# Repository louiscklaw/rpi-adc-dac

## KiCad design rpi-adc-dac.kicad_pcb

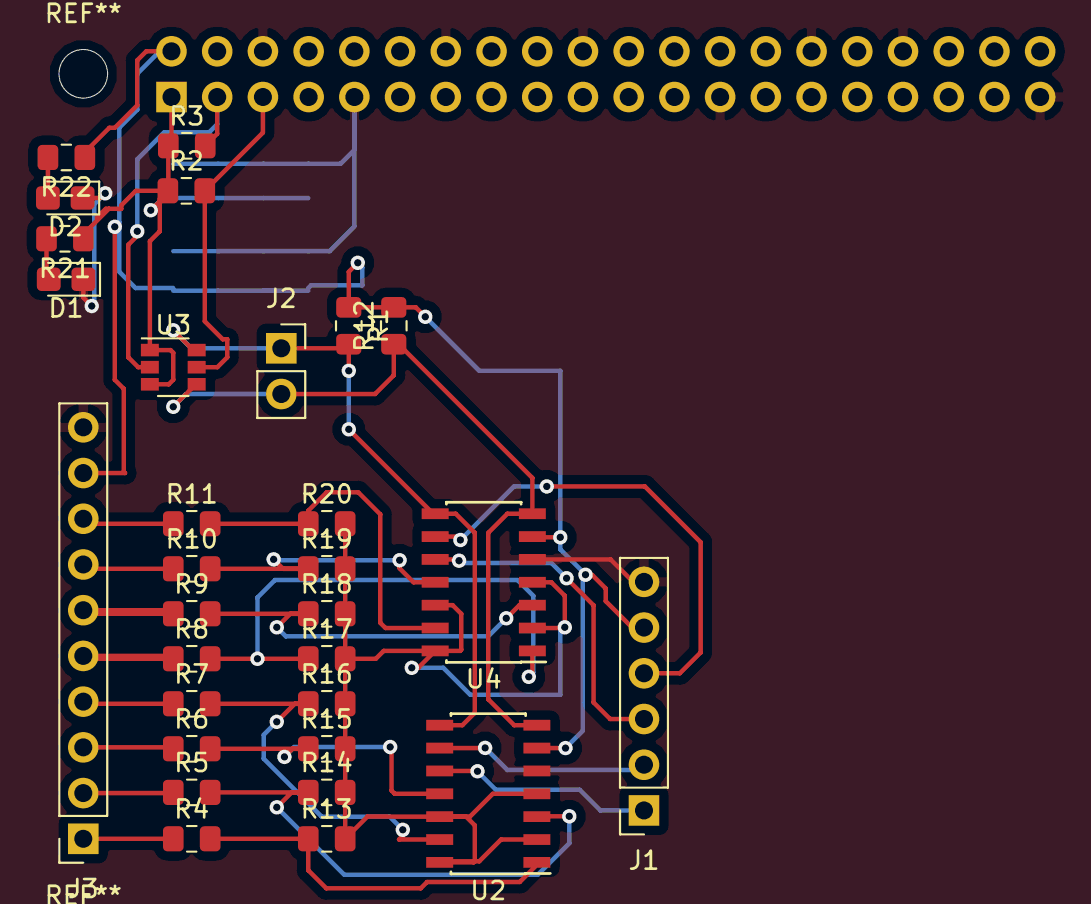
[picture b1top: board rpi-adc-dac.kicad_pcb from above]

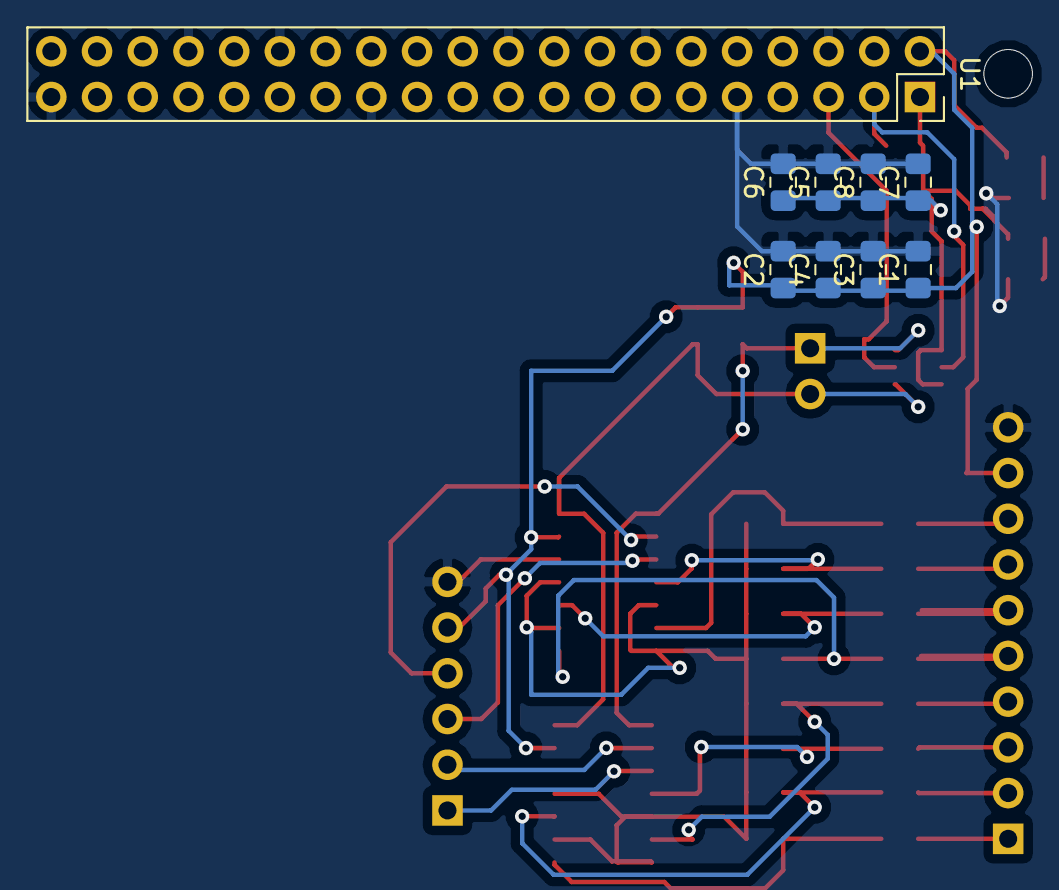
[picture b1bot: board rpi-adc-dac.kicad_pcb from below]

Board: 2 copper layers, 39 parts (9 on the bottom side), 30 nets.

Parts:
C1, C2, C3, C4, C5, C6, C7, C8: 105; C_0805_2012Metric_Pad1.15x1.40mm_HandSolder
D1: 3V3_STATUS; LED_0805_2012Metric_Castellated
D2: 5V_STATUS; LED_0805_2012Metric_Castellated
J1: Conn_01x02; PinSocket_1x06_P2.54mm_Vertical
J2: Conn_01x02; PinSocket_1x02_P2.54mm_Vertical
J3: Conn_01x02; PinSocket_1x10_P2.54mm_Vertical
R1, R2, R3, R4, R5, R6, R7, R8, R9, R11, R12: 103; R_0805_2012Metric_Pad1.15x1.40mm_HandSolder
R10, R14: R; R_0805_2012Metric_Pad1.15x1.40mm_HandSolder
R13, R15, R16, R17, R18, R19, R20: 682; R_0805_2012Metric_Pad1.15x1.40mm_HandSolder
R21: 511; R_0805_2012Metric_Pad1.15x1.40mm_HandSolder
R22: 102; R_0805_2012Metric_Pad1.15x1.40mm_HandSolder
U1: rpi-pin-out; PinSocket_2x20_P2.54mm_Vertical
U2, U4: MCP3424; SOIC-14_3.9x8.7mm_P1.27mm
U3: FDC6301N; SuperSOT-6

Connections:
+3V3: C5.1, C6.1, C7.1, C8.1, R2.1, R3.1, R21.1, U1.1, U3.1, U3.3
+5V: C1.1, C2.1, C3.1, C4.1, J1.5, J3.9, R1.1, R12.2, R22.1, U1.2, U2.6, U4.6
/GPIO0: R3.2, U1.3, U3.2
/GPIO1: R2.2, U1.5, U3.5
/SCL: J2.1, R1.2, U2.8, U3.6, U4.8
/SDA: J2.2, R12.1, U2.7, U3.4, U4.7
GND: C1.2, C2.2, C3.2, C4.2, C5.2, C6.2, C7.2, C8.2, D1.1, D2.1, J1.6, J3.10, U1.6, U1.9, U1.14, U1.20, U1.25, U1.30, U1.34, U1.39, U2.5, U4.5
unnamed: D1.2, R21.2
unnamed: D2.2, R22.2
unnamed: J1.1, U2.10
unnamed: J1.2, U2.9
unnamed: J1.3, U4.10
unnamed: J1.4, U4.9
unnamed: J3.1, R4.1
unnamed: J3.2, R5.1
unnamed: J3.3, R6.1
unnamed: J3.4, R7.1
unnamed: J3.5, R8.1
unnamed: J3.6, R9.1
unnamed: J3.7, R10.1
unnamed: J3.8, R11.1
unnamed: R10.2, R19.1, U4.11
unnamed: R11.2, R20.1, U4.13
unnamed: R4.2, R13.1, U2.1
unnamed: R13.2, R14.2, R15.2, R16.2, R17.2, R18.2, R19.2, R20.2, U2.2, U2.4, U2.12, U2.14, U4.2, U4.4, U4.12, U4.14
unnamed: R5.2, R14.1, U2.3
unnamed: R6.2, R15.1, U2.11
unnamed: R7.2, R16.1, U2.13
unnamed: R8.2, R17.1, U4.1
unnamed: R9.2, R18.1, U4.3

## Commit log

2018-10-11 init commit,
2018-10-11 update,
2020-05-06 ci: init travis token,
2020-05-06 ci: init travis build config,
